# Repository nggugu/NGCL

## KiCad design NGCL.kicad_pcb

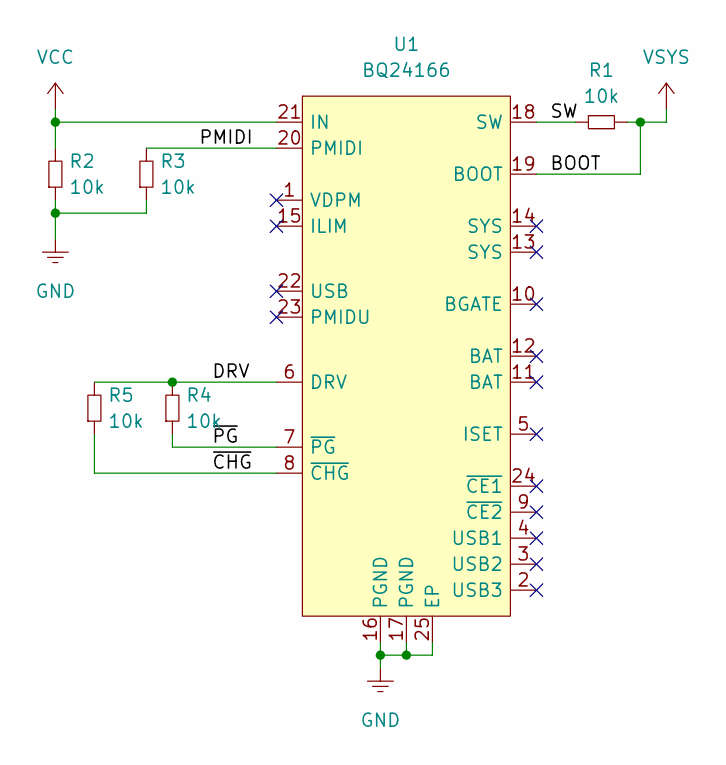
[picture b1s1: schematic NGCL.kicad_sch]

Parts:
R1, R2, R3, R4, R5: 10k; RES0603
U1: BQ24166; QFN50P410X410X100-24P

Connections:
/DRV: R4.2, R5.2, U1.6 (DRV)
/PMIDI: R3.2, U1.20 (PMIDI)
/SW: R1.2, U1.18 (SW)
/~CHG: R5.1, U1.8 (~CHG)
/~PG: R4.1, U1.7 (~PG)
GND: R2.1, R3.1, U1.16 (PGND), U1.17 (PGND), U1.25 (EP)
VCC: R2.2, U1.21 (IN)
VSYS: R1.1, U1.19 (BOOT)

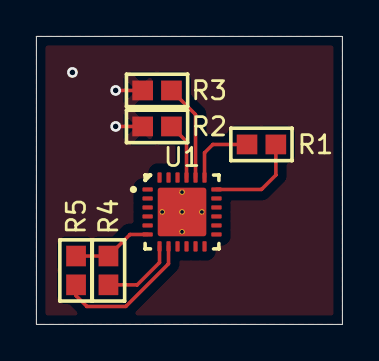
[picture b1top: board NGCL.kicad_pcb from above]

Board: 2 copper layers, 17.0 x 16.0 mm, 6 parts (0 on the bottom side), 8 nets.

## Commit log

2025-01-14 Add .gitignore
2025-02-11 add some passives and audio connector
2025-02-15 Add TLV9154IPWR
2025-02-15 add passives for analog filter
2025-02-15 redraw opamp
2025-02-15 add 100n 0402 cap and fix MP34DT05 fields
2025-04-20 add ppg, 10u, 4u7 0402
